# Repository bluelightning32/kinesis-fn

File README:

This project is about replacing the function keys on the Kinesis Essential and Kinesis Advantage keyboards. The Kinesis Advantage2 has a slightly different keyboard matrix, and as such this project is incompatible with it.

# Required tools

1. Soldering equipment
2. 3d printer
3. Screw driver
4. Diagonal cutters
5. Needle files to file down imperfections in the 3d printed keycaps, and in the replacement circuit boards.

# Bill of materials

1. Left replacement circuit board (order from a circuit board fabricator)
2. Right replacement circuit board (order from a circuit board fabricator)
3. 18 ML1A-11JW cherry mechanical key switches. [Digikey](https://www.digikey.com/en/products/detail/cherry-americas-llc/ML1A-11JW/16990?s=N4IgTCBcDa5gbPAtAWQDIEYCCSMYFIDqSAcgCIgC6AvkA) had the best price I could find, but they are out of stock right now.
4. 2 flat flex cables with 13 pins and 1.25mm pitch. They need to be at least 50mm long, but longer is okay. The pitch (distance between pins) must be correct. If necessary, you can buy a cable with more pins and cut off the extra. I could only find this on [AliExpress](https://www.aliexpress.us/item/3256801627091246.html?spm=a2g0s.12269583.0.0.629a404dzJNHRq&gatewayAdapt=glo2usa4itemAdapt).
5. 2 connectors for the flat flex cables. This [connector](https://www.digikey.com/en/products/detail/molex/0039532135/3160262?s=N4IgTCBcDaIOoFkCMAWArGAbAWgHIBEQBdAXyA) from Digikey should be an exact fit. This [connector](https://www.aliexpress.us/item/2251832596444359.html?spm=a2g0o.order_list.order_list_main.30.21ef1802ZNNYwS&gatewayAdapt=glo2usa4itemAdapt) from AliExpress will fit if you bend the pins a little.
6. 4 screws. #4 3/8 inch pan head. These are common in American hardware stores.
7. Filament for the 3d prints
8. (optional) super glue or gorilla glue to better secure the supports.
9. (optional) nail polish to color the keycaps.

# Directions

Order the left and right circuit boards from a circuit board fabricator. The fabricators want the gerber files, which are in the left-gerbers and right-gerbers directories.

Solder the key switches and the flat flex connectors onto the boards. The components go on the on labeled side, and the solder goes on the labeled side (it also says solder side). Remember to use flux.

Print the keycaps (keys.stl). To make the keycap tabs strong enough, the keycaps need to be printed on their side. This unfortunately reduces the print quality of the embossed labels.

Optionally paint the keycaps with nail polish to hide some of the 3d print imperfections. Do not paint the bottom part of the key cap the inserts into the key switch (it won't fit if you try). Insert the keycaps into the keyswitches. Use the needle file to adjust the keycap support if it does not fit.

Print the supports (support.stl).

Remove the old function keys from the keyboard. They are heat staked in place. So the easiest way is to use diagonal cutters to remove the top of the heat stake. After removing the heat stake, it will be very difficult to use the original function keys again.

Add the supports to the keyboard. They should somewhat snap into place, partially secured with the remaining stems of the heat stakes. The supports will not be fully secure until the screws are added later.

Connect the function row boards to the main board using the flex connectors. Before putting the keyboard back together, hook it up to a computer and verify that the new function keys work. `xev` is a good Linux program to test most of the keys. Use the keyboard's click sound to verify that the last two (keypad and program) work.

If the keys do not work, it might be due to the flex cable. If the flex cable is slightly narrower than the connector, try placing the cable all the way to the left or right of the connector, to align the pins. Also verify that the flex connector is not upside down (silver side faces away from the center of the main board).

Snap the circuit boards into the supports. Secure them with 2 screws each. Verify that the function keys can be pressed smoothly. If the new keycaps bind with the case, then use the needle files to either file the screw holes of the circuit board so that it can be shifted, or file the keycaps.

After the key position has been verified, take the boards back out, squirt some glue in the screw holes, then screw them back in place. This step is optional. The screws mostly hold the boards in place without the glue, but if one presses the keys very hard, the screws alone will not hold, and the board will shift.

Reassemble the keyboard.

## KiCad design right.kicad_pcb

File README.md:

This project is about replacing the function keys on the Kinesis Essential and Kinesis Advantage keyboards. The Kinesis Advantage2 has a slightly different keyboard matrix, and as such this project is incompatible with it.

# Required tools

1. Soldering equipment
2. 3d printer
3. Screw driver
4. Diagonal cutters
5. Needle files to file down imperfections in the 3d printed keycaps, and in the replacement circuit boards.

# Bill of materials

1. Left replacement circuit board (order from a circuit board fabricator)
2. Right replacement circuit board (order from a circuit board fabricator)
3. 18 ML1A-11JW cherry mechanical key switches. [Digikey](https://www.digikey.com/en/products/detail/cherry-americas-llc/ML1A-11JW/16990?s=N4IgTCBcDa5gbPAtAWQDIEYCCSMYFIDqSAcgCIgC6AvkA) had the best price I could find, but they are out of stock right now.
4. 2 flat flex cables with 13 pins and 1.25mm pitch. They need to be at least 50mm long, but longer is okay. The pitch (distance between pins) must be correct. If necessary, you can buy a cable with more pins and cut off the extra. I could only find this on [AliExpress](https://www.aliexpress.us/item/3256801627091246.html?spm=a2g0s.12269583.0.0.629a404dzJNHRq&gatewayAdapt=glo2usa4itemAdapt). On each end of the cable, the traces should be exposed on the top side (see picture later).
5. 2 connectors for the flat flex cables. This [connector](https://www.digikey.com/en/products/detail/molex/0039532135/3160262?s=N4IgTCBcDaIOoFkCMAWArGAbAWgHIBEQBdAXyA) from Digikey should be an exact fit. This [connector](https://www.aliexpress.us/item/2251832596444359.html?spm=a2g0o.order_list.order_list_main.30.21ef1802ZNNYwS&gatewayAdapt=glo2usa4itemAdapt) from AliExpress will fit if you bend the pins a little.
6. 4 screws. #4 3/8 inch pan head. These are common in American hardware stores.
7. Filament for the 3d prints
8. (optional) super glue or gorilla glue to better secure the supports.
9. (optional) nail polish to color the keycaps.

# Directions

Order the left and right circuit boards from a circuit board fabricator. The fabricators want the gerber files, which are in the left-gerbers and right-gerbers directories.

Solder the key switches and the flat flex connectors onto the boards. The components go on the on labeled side, and the solder goes on the labeled side (it also says solder side). Remember to use flux.

Print the keycaps (keys.stl). To make the keycap tabs strong enough, the keycaps need to be printed on their side. This unfortunately reduces the print quality of the embossed labels.

Optionally paint the keycaps with nail polish to hide some of the 3d print imperfections. Do not paint the bottom part of the key cap the inserts into the key switch (it won't fit if you try). Insert the keycaps into the keyswitches. Use the needle file to adjust the keycap support if it does not fit.

Print the supports (support.stl).

Remove the old function keys from the keyboard. They are heat staked in place. So the easiest way is to use diagonal cutters to remove the top of the heat stake. After removing the heat stake, it will be very difficult to use the original function keys again.

Add the supports to the keyboard. They should somewhat snap into place, partially secured with the remaining stems of the heat stakes. The supports will not be fully secure until the screws are added later.

Each end of the flex cable should have the traces exposed on the same side. Here is the top and bottom of an example flex connector: 

Connect the function row boards to the main board using the flex connectors. Before putting the keyboard back together, hook it up to a computer and verify that the new function keys work. `xev` is a good Linux program to test most of the keys. Use the keyboard's click sound to verify that the last two (keypad and program) work.

If the keys do not work, it might be due to the flex cable. If the flex cable is slightly narrower than the connector, try placing the cable all the way to the left or right of the connector, to align the pins. Also verify that the flex connector is not upside down (silver side faces away from the center of the main board).

Snap the circuit boards into the supports. Secure them with 2 screws each. Verify that the function keys can be pressed smoothly. If the new keycaps bind with the case, then use the needle files to either file the screw holes of the circuit board so that it can be shifted, or file the keycaps.

After the key position has been verified, take the boards back out, squirt some glue in the screw holes, then screw them back in place. This step is optional. The screws mostly hold the boards in place without the glue, but if one presses the keys very hard, the screws alone will not hold, and the board will shift.

Reassemble the keyboard.

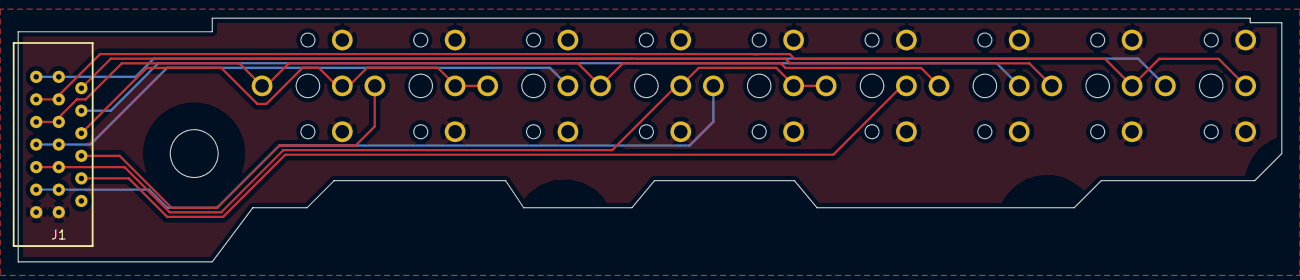
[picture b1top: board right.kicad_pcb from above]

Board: 2 copper layers, 140.0 x 27.0 mm, 11 parts (0 on the bottom side), 12 nets.

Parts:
F9, F10, F11, F12: ML1A_11JW; ML1A-11JW
H1: MountingHole_5.3mm_M5
J1: FFC_Connector_13P
KP1: ML1A_11JW; ML1A-11JW
P-B1: ML1A_11JW; ML1A-11JW
P-S1: ML1A_11JW; ML1A-11JW
PG1: ML1A_11JW; ML1A-11JW
S-L1: ML1A_11JW; ML1A-11JW

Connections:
GND: F9.1, F9.3, F10.1, F10.3, F11.1, F11.3, F12.1, F12.3, J1.13, J1.13B, KP1.1, KP1.3, P-B1.1, P-B1.3, P-S1.1, P-S1.3, PG1.1, PG1.3, S-L1.1, S-L1.3
unnamed: F9.2, F10.2, F11.4, J1.6
unnamed: F10.4, J1.8
unnamed: F11.2, J1.7, J1.7B
unnamed: F12.2, J1.9, J1.9B, P-S1.2, S-L1.4
unnamed: F9.4, F12.4, J1.5, J1.5B, P-B1.4
unnamed: J1.1, J1.1B, PG1.4
unnamed: J1.2, KP1.4
unnamed: J1.3, J1.3B, KP1.2, PG1.2
unnamed: J1.4, P-B1.2
unnamed: J1.10, S-L1.2
unnamed: J1.11, J1.11B, P-S1.4

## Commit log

2022-04-30 V1.1
2022-04-30 Increase ffc connector hole size to 0.6 mm
    The wires on the connector actually measure up to 0.57 mm.
2022-05-01 First attempt at key cap 3d print
2022-05-01 Make the key text thicker so that cura prints it
2022-05-04 Make the key caps hollow inside
    This allows the prongs to be chamfered to reduce their stress point on the key
    cap.
2022-05-05 Revert "Make the key caps hollow inside"
    This reverts commit 5169b3acb901a9deba7ef0b5a501670e830176ee.
    It didn't fix the stress point.
2022-05-05 Print the keycaps sideways to strengthen the prongs
2022-05-07 Add the support
    The support does not have the tabs on the bottom yet.
2022-05-07 Update the support model
    Add the slot cuts.
2022-05-07 Remove more from the left corner of the support piece
2022-05-07 Angle the slots in the support
2022-05-07 Adjust support
    1. Increase the size of the cut on the lower left.
    2. Move the first 3 screw holes down.
2022-05-07 Slant the top of the support
2022-05-07 Adjust support
    1. Move the first screw hole so that it aligns better with the plastic
    underneath.
    2. Increase the diameter of screw anchors 1 through 3.
    3. Taper the screw anchors so that the screw does not grab on to the
    unreinforced anchor and separate the layers.
2022-05-07 Make the cut around screw hole 1 in the support a little smaller
    There was extra room between the board and the screw anchor.
2022-05-07 Add the left support
2022-05-08 Reduce the support height
2022-05-08 Shift the key switches on the right PCB over 0.6 mm
2023-08-06 Add a MIT license
2023-08-07 Add a README and pictures.
2023-08-07 Rename the README file so that it hopefully renders correctly.
2026-03-20 Be more specific about which flex cables are acceptable
    Fixes #1

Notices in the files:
right.kicad_pcb:
License: MIT
